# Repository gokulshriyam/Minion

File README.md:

1. PRODUCT :

Minion is for all electricity consumers across the world to help reduce their power costs at an affordable price point using "user friendly" products & analysis.

As there are many IOT Smart Energy Devices in the market that ensures energy efficiency and cost saving but it makes monthly electric bills doubling or tripling every month, with no increase in energy usage. 

We had carefully read solutions of all existing smart meters across the world and identified the perfect use case which ensures 100% energy efficiency and cost saving to the electricity consumers

Minion is a single device (size: 39x49 Millimeter - World's smallest pocket energy auditor) with Wi-Fi,LORA,3G/4G Connectivity which will fit inside the breaker panel (next to utility meter like addon) with single sensor clamp connection after the utility meter.

This Minion will perform appliance/device/tool/equipment wise real-time energy analytics. It will also perform Predictive analytics & maintenance of assets (Hospital, Industrial, Manufacturing/factories, Hospitality, Retail) which rescues the high cost assets from breakdown and also lowers the insurance costs. It schedules maintenance which will ensure and extend the life-time of assets beyond insurance time.

Our Minion is also Solar friendly/compatible. It has the ability to measure generation and consumption readings (acts as net meter) and performs real time & predictive analytics. 

All the analytics are done on the cloud and enable users to experience the results through our SaaS - Windows application, Android & IoS Apps.

Our Minion provides three steps for ensuring 100% energy efficiency and cost saving

1. Realtime analytics - Let's user know what is he/she spending for at appliance level at any sectors (Residential, Hospitality, Hospitals, Industrial and more)

2. Predictive analytics - Reduces surprises in energy bills and User's can easily predict the energy usage and bills and schedule accordingly. This would be very useful for sectors running high cost assets which will prevent from breakdown and increase the efficiency of the assets.

3. Operating System (OS) - The predictive analytics with data and sensors leads to Operating system which ensures 100% of efficiency & cost saving. Without the help of human interfering, Our OS will perform automation inside buildings.

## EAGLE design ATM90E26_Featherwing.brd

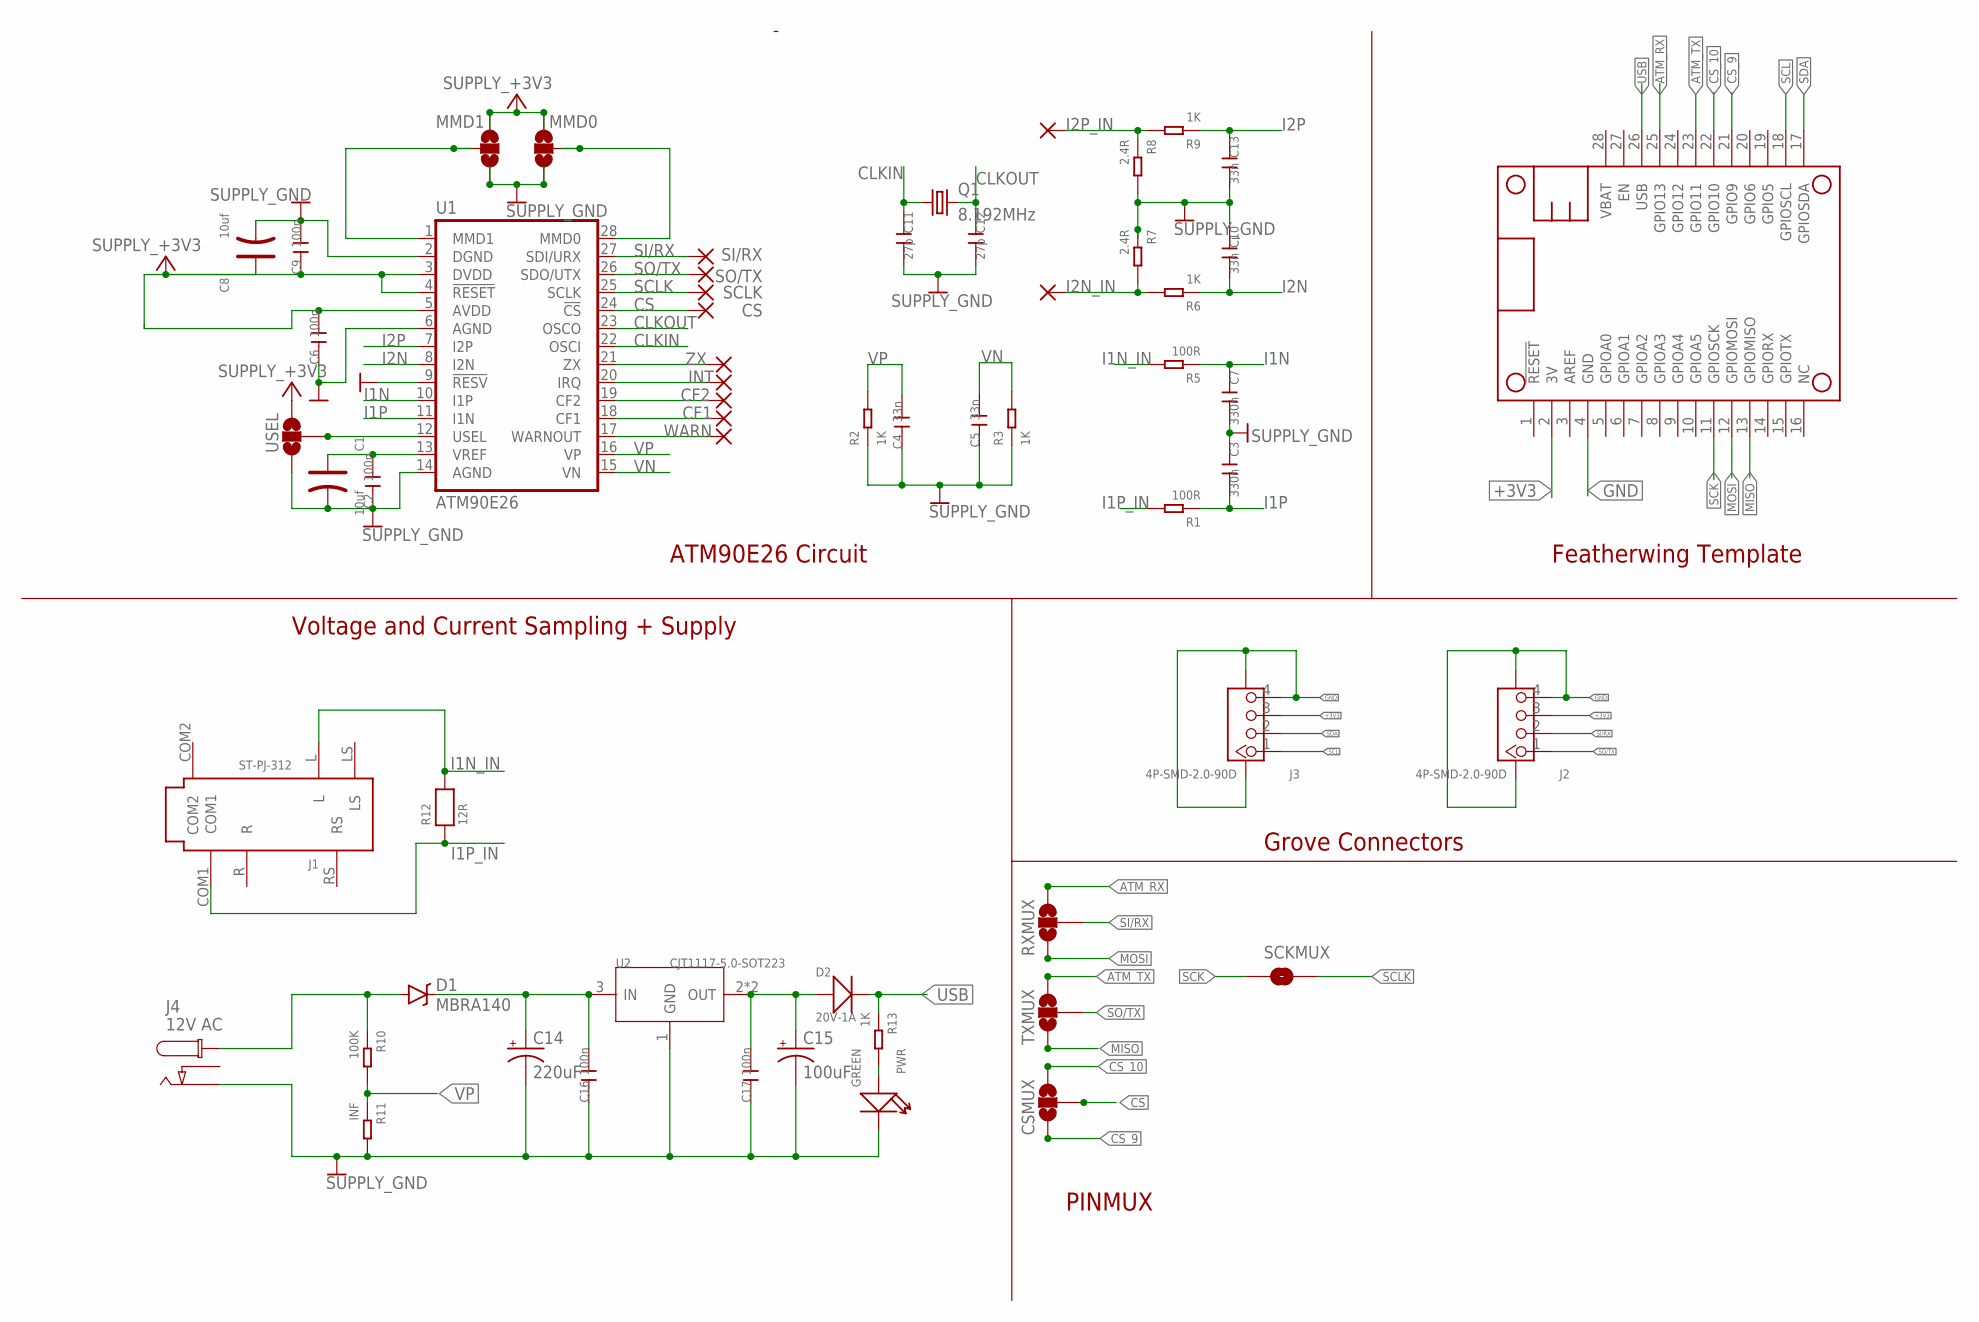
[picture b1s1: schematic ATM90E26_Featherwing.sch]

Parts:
C1, C8: 10uf; AVX-A
C2, C6, C9, C16, C17: 100n; C0603
C3, C7: 330n; C0603
C4, C5, C10, C13: 33n; C0603
C11, C12: 27p; C0603
C14: 220uF; 140CLH-1010
C15: 100uF; 153CLV-0605
CF1, CF2: WIREPADSMD1,27-254; SMD1,27-2,54
CS: WIREPADSMD1,27-254; SMD1,27-2,54
CSMUX: JUMPER-PAD-3-NOYES_SILK; PAD-JUMPER-3-NO_YES_SILK
D1: MBRA140; SMA-DIODE
D2: 20V-1A; SOD-123
I2N_IN, I2P_IN: WIREPADSMD1,27-254; SMD1,27-2,54
INT: WIREPADSMD1,27-254; SMD1,27-2,54
J1: ST-PJ-312; AUDIO6P-SMD-3.5-14.0X6.4X5.0MM
J2, J3: 4P-SMD-2.0-90D; HW4-SMD-2.0-90D
J4: 12V AC; DC_BARREL_JACK_SMD_2MM
MMD0, MMD1: JUMPER-PAD-3-NOFULL_BOX_SILK; PAD-JUMPER-3-NO_YES_SILK_FULL_BOX
MS1: FEATHERWING_NODIM; FEATHERWING_DIM
PWR: GREEN; LED-0603
Q1: 8.192MHz; HC49UP
R1, R5: 100R; R0603
R2, R3, R6, R9, R13: 1K; R0603
R7, R8: 2.4R; R0603
R10: 100K; R0603
R11: INF; R0603
R12: 12R; 0805
RXMUX: JUMPER-PAD-3-NOYES_SILK; PAD-JUMPER-3-NO_YES_SILK
SCKMUX: JUMPER-PAD-2-NOYES_SILK; PAD-JUMPER-2-NO_YES_SILK
SCLK: WIREPADSMD1,27-254; SMD1,27-2,54
SI/RX: WIREPADSMD1,27-254; SMD1,27-2,54
SO/TX: WIREPADSMD1,27-254; SMD1,27-2,54
TXMUX: JUMPER-PAD-3-NOYES_SILK; PAD-JUMPER-3-NO_YES_SILK
U1: ATM90E26; SSOP-28
U2: CJT1117-5.0-SOT223; SOT-223
USEL: JUMPER-PAD-3-NOFULL_BOX_SILK; PAD-JUMPER-3-NO_YES_SILK_FULL_BOX
WARN: WIREPADSMD1,27-254; SMD1,27-2,54
ZX: WIREPADSMD1,27-254; SMD1,27-2,54

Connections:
+3V3: C6.2, C8.+, C9.1, J2.3, J3.3, MMD0.3, MMD1.1, MS1.2 (3V), U1.3 (DVDD), U1.4 (!RESET), U1.5 (AVDD), USEL.3
ATM_RX: MS1.25 (GPIO13), RXMUX.3
ATM_TX: MS1.23 (GPIO11), TXMUX.3
CLKIN: C11.1, Q1.1, U1.22 (OSCI)
CLKOUT: C12.1, Q1.2, U1.23 (OSCO)
CS: CS.1, CSMUX.2, U1.24 (!CS)
CS_9: CSMUX.1, MS1.21 (GPIO9)
CS_10: CSMUX.3, MS1.22 (GPIO10)
GND: C1.-, C2.1, C3.1, C4.1, C5.1, C6.1, C7.2, C8.-, C9.2, C10.1, C11.2, C12.2, C13.2, C14.-, C15.-, C16.1, C17.1, J2.4, J2.SS1, J2.SS2, J3.4, J3.SS1, J3.SS2, J4.P2, MMD0.1, MMD1.3, MS1.4 (GND), PWR.-, R2.1, R3.1, R7.1, R8.2, R11.2, U1.2 (DGND), U1.6 (AGND), U1.9 (!RESV), U1.14 (AGND), U2.1 (GND), USEL.1
I1N: C7.1, R5.1, U1.10 (I1P)
I1N_IN: J1.L, R5.2, R12.2
I1P: C3.2, R1.1, U1.11 (I1N)
I1P_IN: J1.COM1, R1.2, R12.1
I2N: C10.2, R6.1, U1.8 (I2N)
I2N_IN: I2N_IN.1, R6.2, R7.2
I2P: C13.1, R9.1, U1.7 (I2P)
I2P_IN: I2P_IN.1, R8.1, R9.2
MISO: MS1.13 (GPIOMISO), TXMUX.1
MOSI: MS1.12 (GPIOMOSI), RXMUX.1
unnamed: MMD1.2, U1.1 (MMD1)
unnamed: MMD0.2, U1.28 (MMD0)
unnamed: D1.A, J4.P1@2 (P1), R10.1
unnamed: C14.+, C16.2, D1.C, U2.3 (IN)
unnamed: PWR.+, R13.2
unnamed: CF1.1, U1.18 (CF1)
unnamed: CF2.1, U1.19 (CF2)
unnamed: U1.12 (USEL), USEL.2
unnamed: U1.21 (ZX), ZX.1
unnamed: INT.1, U1.20 (IRQ)
unnamed: U1.17 (WARNOUT), WARN.1
SCK: MS1.11 (GPIOSCK), SCKMUX.1
SCL: J3.1, MS1.18 (GPIOSCL)
SCLK: SCKMUX.2, SCLK.1, U1.25 (SCLK)
SDA: J3.2, MS1.17 (GPIOSDA)
SI/RX: J2.2, RXMUX.2, SI/RX.1, U1.27 (SDI/URX)
SO/TX: J2.1, SO/TX.1, TXMUX.2, U1.26 (SDO/UTX)
USB: D2.-, MS1.26 (USB), R13.1
VN: C5.2, R3.2, U1.15 (VN)
VP: C4.2, R2.2, R10.2, R11.1, U1.16 (VP)
VREF: C1.+, C2.2, U1.13 (VREF)
V_OUT: C15.+, C17.2, D2.+, U2.2 (OUT), U2.TER (OUT)

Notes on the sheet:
ATM90E26 Circuit
Featherwing Template
Voltage and Current Sampling + Supply
Grove Connectors
PINMUX

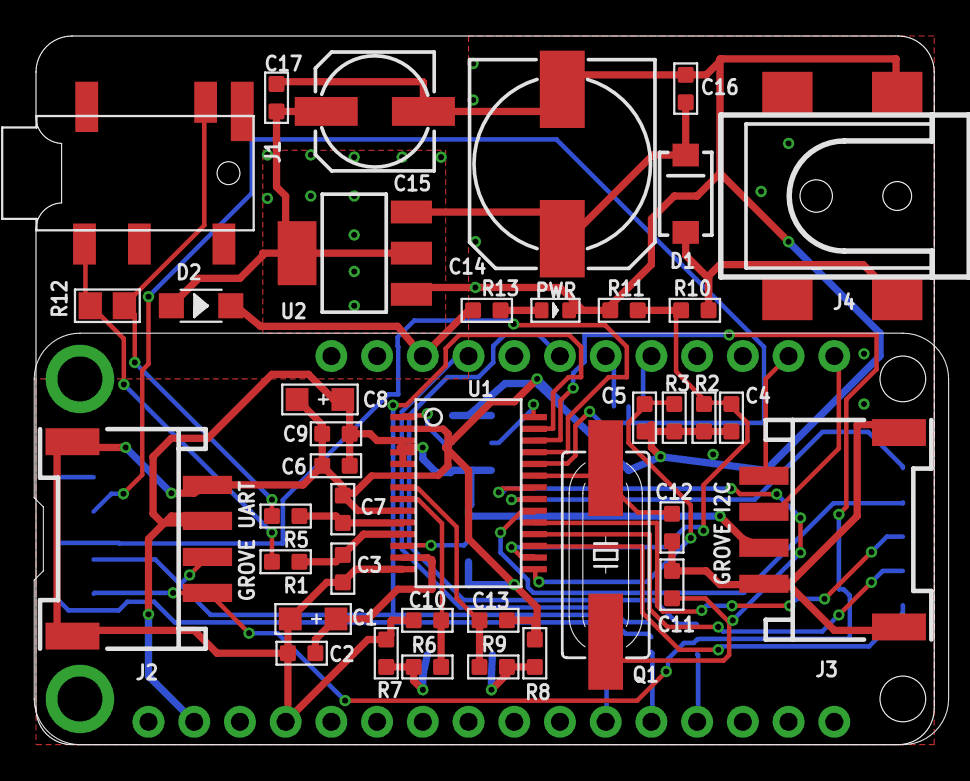
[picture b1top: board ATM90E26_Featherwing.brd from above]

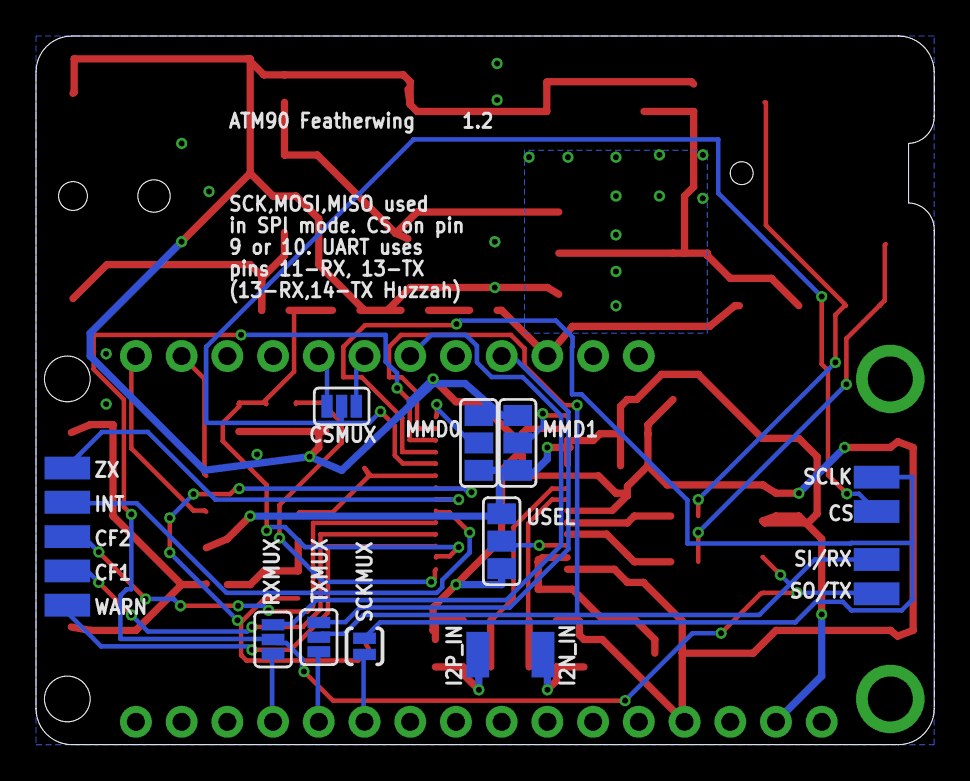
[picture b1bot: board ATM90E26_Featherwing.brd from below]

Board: 2 copper layers, 49.9 x 39.4 mm, 58 parts (18 on the bottom side), 41 nets.

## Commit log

2017-04-09 Set theme jekyll-theme-hacker

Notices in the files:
parts and their libraries:
SparkFun-DiscreteSemi: Licensing: Creative Commons ShareAlike 4.0 International - https://creativecommons.org/licenses/by-sa/4.0
